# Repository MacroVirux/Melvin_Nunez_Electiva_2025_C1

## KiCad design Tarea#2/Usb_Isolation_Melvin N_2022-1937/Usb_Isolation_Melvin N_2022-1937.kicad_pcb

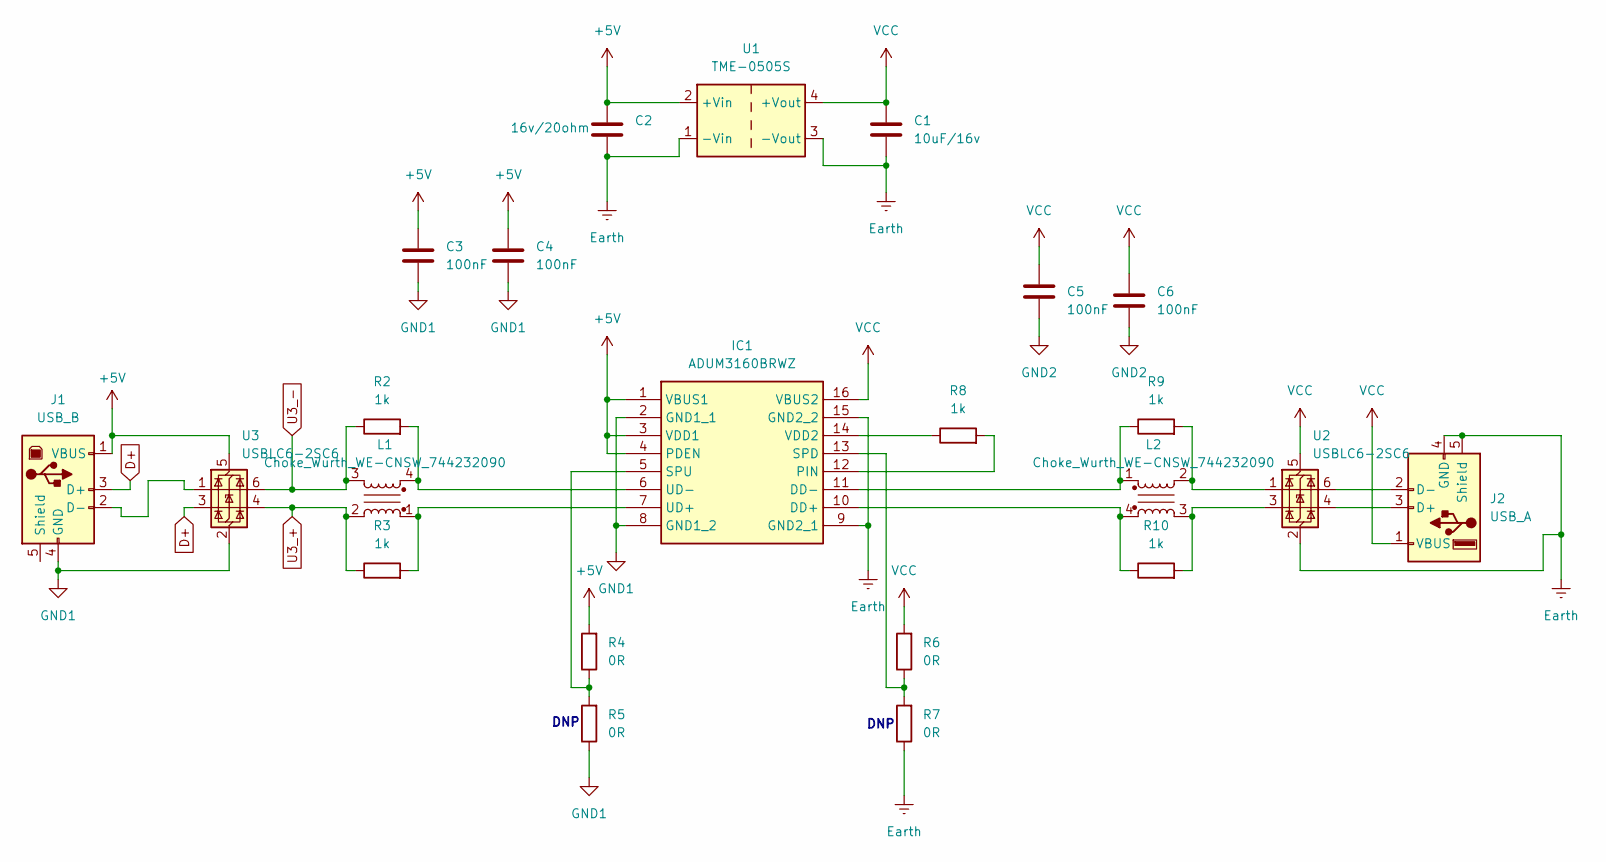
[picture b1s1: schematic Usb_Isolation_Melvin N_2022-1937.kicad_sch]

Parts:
C1: 10uF/16v; C_0603_1608Metric
C2: 16v/20ohm; C_0603_1608Metric
C3, C4, C5, C6: 100nF; C_0603_1608Metric
IC1: ADUM3160BRWZ; SOIC127P1032X265-16; Manufacturer_Part_Number ADUM3160BRWZ; Mouser Part Number 584-ADUM3160BRWZ
J1: USB_B; USB_B_Lumberg_2411_02_Horizontal
J2: USB_A; USB_A_Molex_67643_Horizontal
L1, L2: Choke_Wurth_WE-CNSW_744232090; L_CommonMode_Wurth_WE-CNSW-1206
R2, R3, R8, R9, R10: 1k; R_0603_1608Metric
R4, R5, R6, R7: 0R; R_0603_1608Metric
U1: TME-0505S; Converter_DCDC_TRACO_TME_03xxS_05xxS_12xxS_Single_THT
U2, U3: USBLC6-2SC6; SOT-23-6

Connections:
+5V: C2.1, C3.1, C4.1, IC1.1 (VBUS1), IC1.3 (VDD1), IC1.4 (PDEN), J1.1 (VBUS), R4.2, U1.2 (+Vin), U3.5 (VBUS)
D+: J1.3 (D+), U3.3 (I/O2)
Earth: C1.2, C2.2, IC1.9 (GND2_1), IC1.15 (GND2_2), J2.4 (GND), J2.5 (Shield), R7.1, U1.1 (-Vin), U1.3 (-Vout), U2.2 (GND)
GND1: C3.2, C4.2, IC1.2 (GND1_1), IC1.8 (GND1_2), J1.4 (GND), R5.1, U3.2 (GND)
GND2: C5.2, C6.2
unnamed: IC1.10 (DD+), L2.4, R10.1
unnamed: IC1.11 (DD-), L2.1, R9.1
unnamed: IC1.12 (PIN), R8.2
unnamed: IC1.13 (SPD), R6.1, R7.2
unnamed: IC1.5 (SPU), R4.1, R5.2
unnamed: IC1.7 (UD+), L1.1, R3.2
unnamed: IC1.6 (UD-), L1.4, R2.2
unnamed: IC1.14 (VDD2), R8.1
unnamed: J1.2 (D-), U3.1 (I/O1)
unnamed: J2.3 (D+), U2.4 (I/O2)
unnamed: J2.2 (D-), U2.6 (I/O1)
unnamed: L2.2, R9.2, U2.1 (I/O1)
unnamed: L2.3, R10.2, U2.3 (I/O2)
U3_+: L1.2, R3.1, U3.4 (I/O2)
U3_-: L1.3, R2.1, U3.6 (I/O1)
VCC: C1.1, C5.1, C6.1, IC1.16 (VBUS2), J2.1 (VBUS), R6.2, U1.4 (+Vout), U2.5 (VBUS)

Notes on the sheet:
DNP

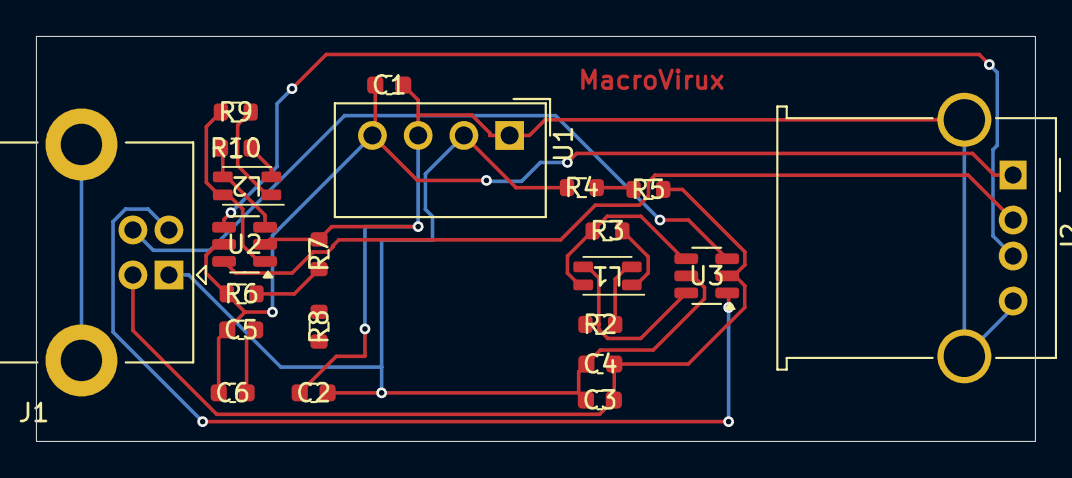
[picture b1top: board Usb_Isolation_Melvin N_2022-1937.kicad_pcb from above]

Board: 2 copper layers, 55.5 x 22.5 mm, 22 parts (0 on the bottom side), 19 nets.

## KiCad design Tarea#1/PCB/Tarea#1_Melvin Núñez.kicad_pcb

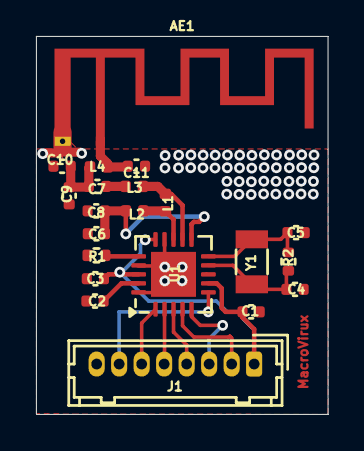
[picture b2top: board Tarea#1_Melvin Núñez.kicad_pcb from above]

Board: 2 copper layers, 16.2 x 21.0 mm, 21 parts (0 on the bottom side), 18 nets.

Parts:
AE1: Antenna; Texas_SWRA117D_2.4GHz_Right
C1: 10n; C_0402_1005Metric
C2: 33n; C_0402_1005Metric
C3: 1n; C_0402_1005Metric
C4, C5: 22p; C_0402_1005Metric
C6, C8: C_0402_1005Metric
C7: 1p5; C_0402_1005Metric
C9: 1p; C_0402_1005Metric
C10, C11: Cx; C_0402_1005Metric
J1: Conn_01x08_Pin; Hirose_DF13-08P-1.25DSA_1x08_P1.25mm_Vertical
L1: 8n2; L_0402_1005Metric
L2: 2n7; L_0402_1005Metric
L3: 3n9; L_0402_1005Metric
L4: Lx; L_0402_1005Metric
R1: 22k; R_0402_1005Metric
R2: 10M; R_0402_1005Metric
U1: NRF24L01; QFN-20-1EP_4x4mm_P0.5mm_EP2.5x2.5mm
Y1: 16MHz; Crystal_SMD_3215-2Pin_3.2x1.5mm

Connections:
GND: C1.2, C2.2, C3.2, C4.2, C5.2, C6.2, C8.2, C9.2, C10.2, C11.2, J1.8, R1.2, U1.8 (VSS), U1.14 (VSS), U1.17 (VSS), U1.20 (VSS)
unnamed: AE1.1 (A), C11.1, L4.2
unnamed: C7.1, L3.2
unnamed: C7.2, C9.1, C10.1, L4.1
unnamed: J1.2, U1.4 (MOSI)
unnamed: J1.3, U1.5 (MISO)
unnamed: J1.4, U1.3 (SCK)
unnamed: J1.5, U1.2 (CSN)
unnamed: J1.6, U1.1 (CE)
unnamed: J1.7, U1.6 (IRQ)
unnamed: L1.1, L3.1, U1.12 (ANT1)
unnamed: L1.2, L2.1, U1.13 (ANT2)
unnamed: C2.1, U1.19 (DVDD)
unnamed: R1.1, U1.16 (IREF)
unnamed: C6.1, C8.1, L2.2, U1.11 (VDD_PA)
unnamed: C5.1, R2.2, U1.10 (XC1), Y1.2
unnamed: C4.1, R2.1, U1.9 (XC2), Y1.1
VDD: C1.1, C3.1, J1.1, U1.7 (VDD), U1.15 (VDD), U1.18 (VDD)

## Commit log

2025-01-27 Create algo.
2025-04-25 Create CASE(CARCASA)
    Es la el case que habíamos hecho con Nico pero con Retoques propios.
2025-04-26 Create Diseños (Case)
    Arreglitos
